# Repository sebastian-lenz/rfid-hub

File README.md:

# RFID Hub

The RFID Hub is a C++ project designed to utilize the Raspberry Pi Pico 
microcontroller to interface with up to four RFID readers. Each RFID reader 
acts as a unique keyboard input, allowing  users to simulate keystrokes by
presenting RFID tags to the readers. 

## Compiling

This project uses Platform.IO, please visit https://platformio.org/ to find
out more. After installing Platform.IO this project can be build using the 
following command:

```
$ pio run
```

If a Raspberry Pico is connected the project can be build and uploaded to
the board using the following command:

```
$ pio run -t upload -e pico
```

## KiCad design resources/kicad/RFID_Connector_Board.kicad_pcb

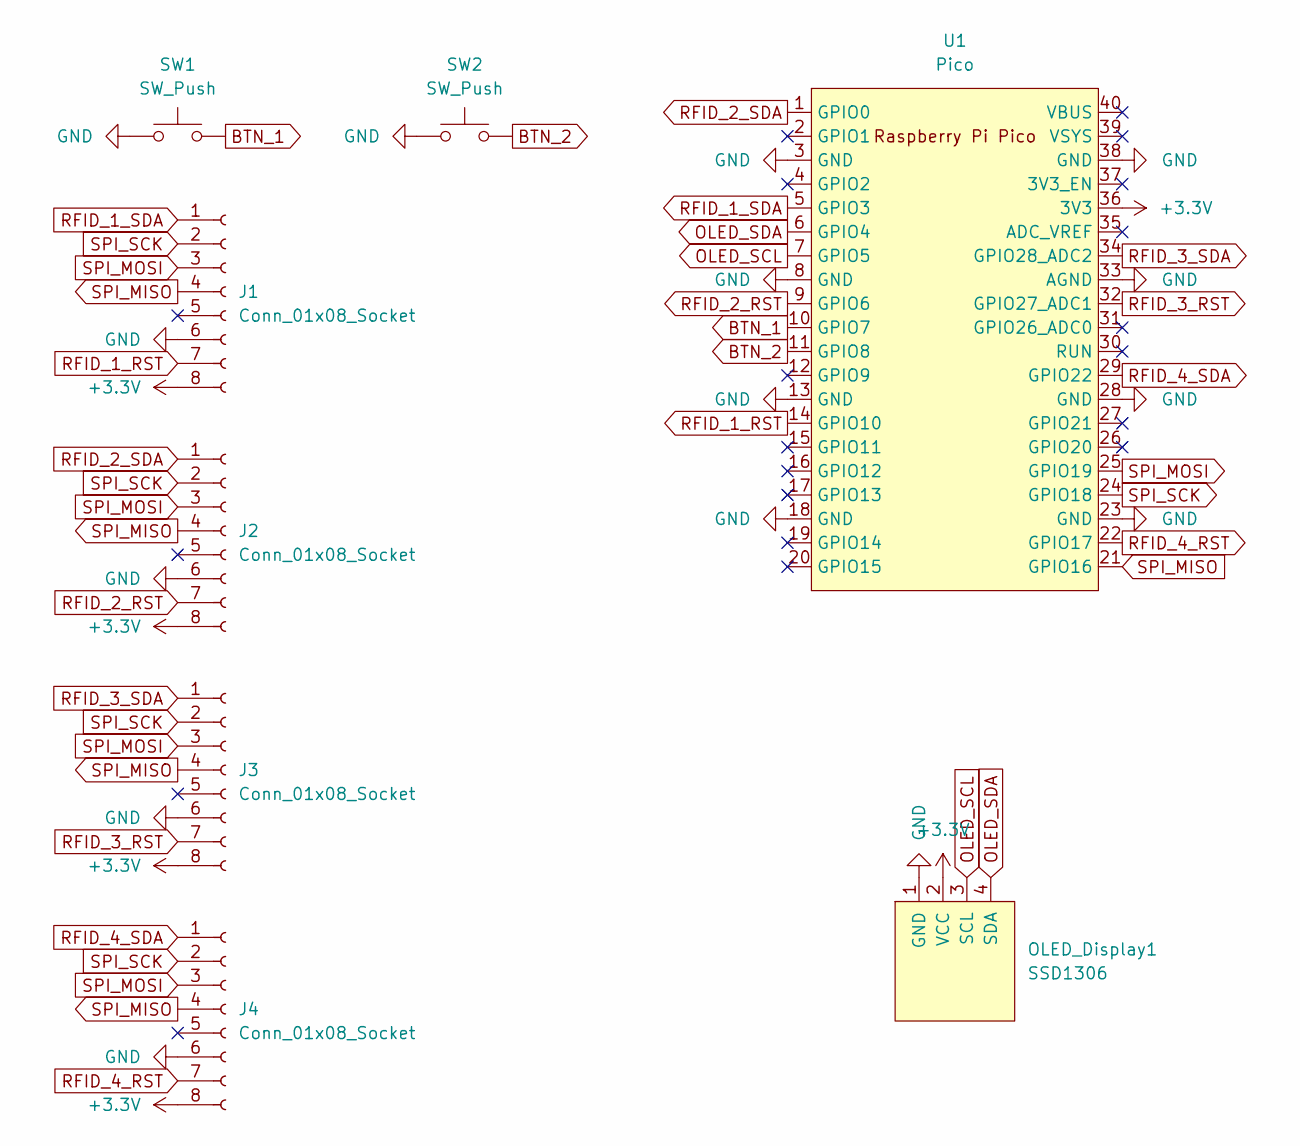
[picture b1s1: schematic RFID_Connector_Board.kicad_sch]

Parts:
J1, J2, J3, J4: Conn_01x08_Socket; JST_EH_S8B-EH_1x08_P2.50mm_Horizontal
OLED_Display1: SSD1306; 128x64OLED_1.3
SW1, SW2: SW_Push; SW_PUSH_6mm_H7.3mm
U1: Pico; RPi_Pico_SMD_TH_Simple

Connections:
+3.3V: J1.8, J2.8, J3.8, J4.8, OLED_Display1.2 (VCC), U1.36 (3V3)
BTN_1: SW1.2, U1.10 (GPIO7)
BTN_2: SW2.2, U1.11 (GPIO8)
GND: J1.6, J2.6, J3.6, J4.6, OLED_Display1.1 (GND), SW1.1, SW2.1, U1.3 (GND), U1.8 (GND), U1.13 (GND), U1.18 (GND), U1.23 (GND), U1.28 (GND), U1.33 (AGND), U1.38 (GND)
OLED_SCL: OLED_Display1.3 (SCL), U1.7 (GPIO5)
OLED_SDA: OLED_Display1.4 (SDA), U1.6 (GPIO4)
RFID_1_RST: J1.7, U1.14 (GPIO10)
RFID_1_SDA: J1.1, U1.5 (GPIO3)
RFID_2_RST: J2.7, U1.9 (GPIO6)
RFID_2_SDA: J2.1, U1.1 (GPIO0)
RFID_3_RST: J3.7, U1.32 (GPIO27_ADC1)
RFID_3_SDA: J3.1, U1.34 (GPIO28_ADC2)
RFID_4_RST: J4.7, U1.22 (GPIO17)
RFID_4_SDA: J4.1, U1.29 (GPIO22)
SPI_MISO: J1.4, J2.4, J3.4, J4.4, U1.21 (GPIO16)
SPI_MOSI: J1.3, J2.3, J3.3, J4.3, U1.25 (GPIO19)
SPI_SCK: J1.2, J2.2, J3.2, J4.2, U1.24 (GPIO18)

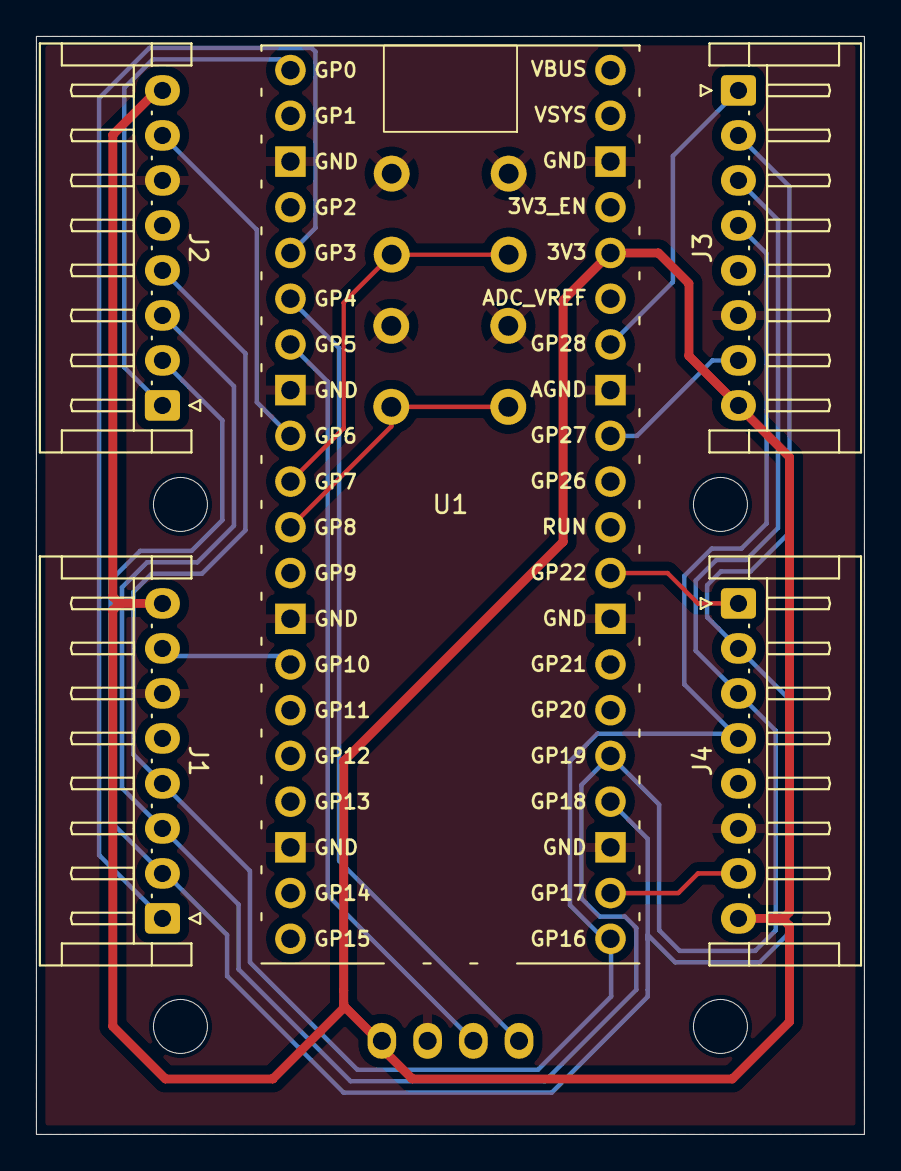
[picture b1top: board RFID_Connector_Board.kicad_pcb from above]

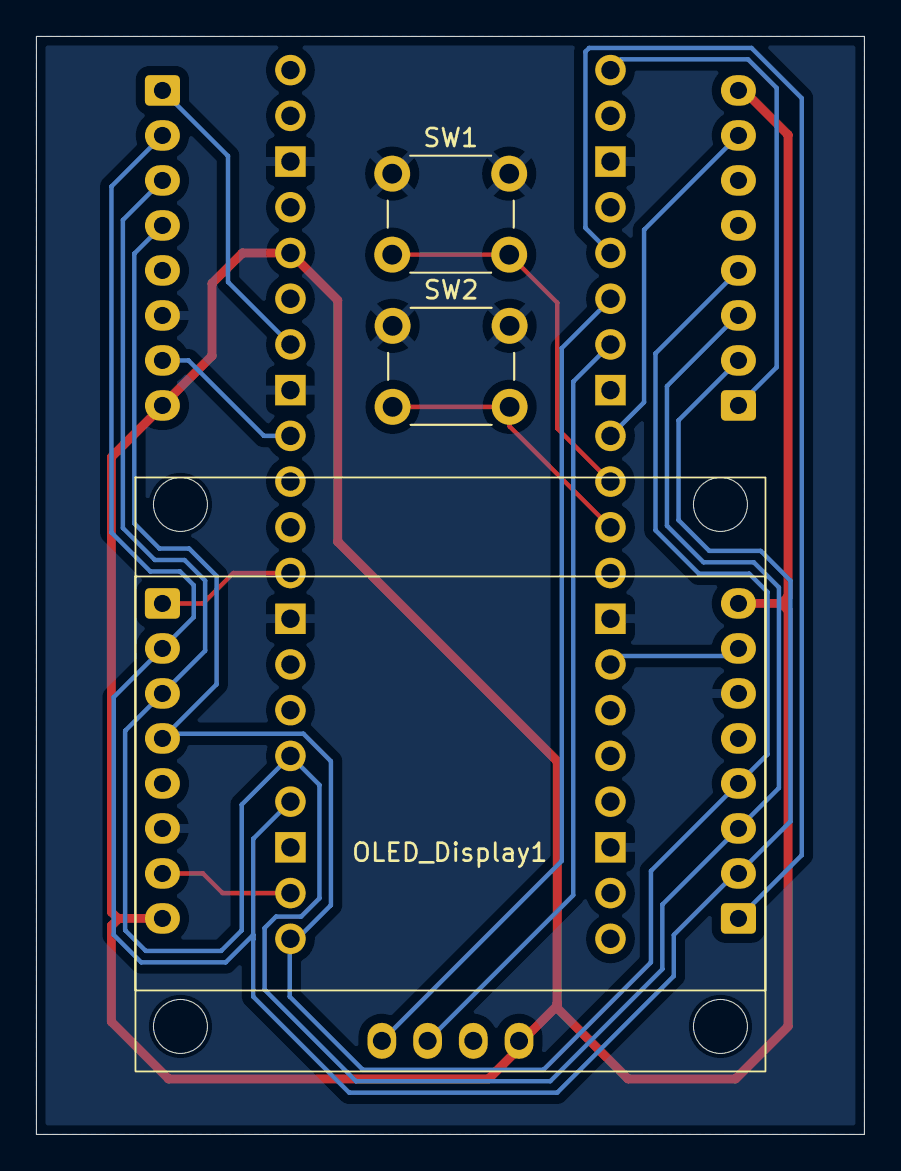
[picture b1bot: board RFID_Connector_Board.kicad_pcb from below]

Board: 2 copper layers, 46.0 x 61.0 mm, 8 parts (3 on the bottom side), 17 nets.

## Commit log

2024-06-26 Update button pins
2024-06-26 Add KiCad project
